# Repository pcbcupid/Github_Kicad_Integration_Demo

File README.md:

View this project on [CADLAB.io](https://cadlab.io/project/26925). 

# Github_Kicad_Integration_Demo
This is a test repository to learn how to integrate KiCad + Git + Github

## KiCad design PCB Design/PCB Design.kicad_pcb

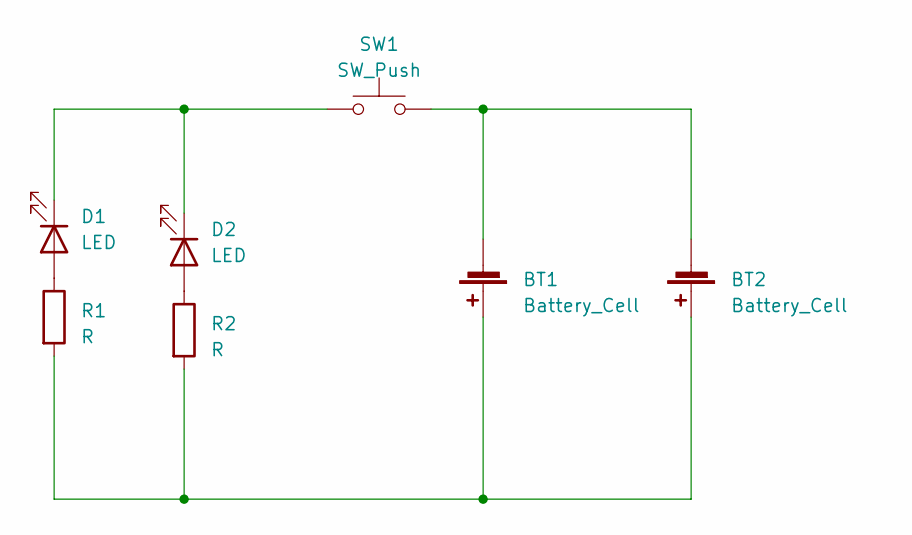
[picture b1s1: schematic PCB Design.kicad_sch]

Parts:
BT1, BT2: Battery_Cell; Molex_KK-254_AE-6410-02A_1x02_P2.54mm_Vertical
D1, D2: LED; LED_0805_2012Metric_Pad1.15x1.40mm_HandSolder
R1, R2: R; R_0805_2012Metric_Pad1.20x1.40mm_HandSolder
SW1: SW_Push; SW_Push_1P1T_NO_CK_KMR2

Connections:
unnamed: BT1.1 (+), BT2.1 (+), R1.2, R2.2
unnamed: BT1.2 (-), BT2.2 (-), SW1.2
unnamed: D1.2 (A), R1.1
unnamed: D1.1 (K), D2.1 (K), SW1.1
unnamed: D2.2 (A), R2.1

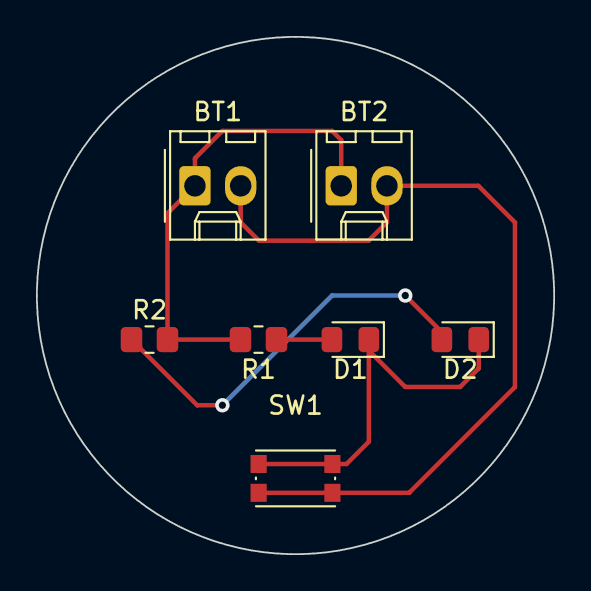
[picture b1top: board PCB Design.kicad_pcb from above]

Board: 2 copper layers, 28.7 x 28.7 mm, 7 parts (0 on the bottom side), 5 nets.

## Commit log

2023-05-03 Intial commit
2023-05-03 Schmeatic added
2023-05-03 gitignore file updated
2023-05-03 THT Footprint assigned
2023-05-03 Component placement is done
2023-05-03 Routing done
2023-05-03 Documentation added
2023-05-03 Initial Mechanical Model and dimension added
2023-05-03 SMD Footprint assignment done
2023-05-03 SMD Placement done
2023-05-03 SMD Routing done
2023-05-09 Backlink to CADLAB.io has been added.
2023-05-10 Libraries added
